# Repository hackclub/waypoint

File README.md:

# Waypoint

Website still a Work in progress! Come back in a week or so!

## Overview

Waypoint is a You Ship, We Ship (YSWS) program where you design your own ROS2 robot.

### You ship:

- A PCB design for your robot
- A chassis design in .STEP format
- A starter ROS2 package for the robot

### We send you:

- A custom Hack Club Waypoint kit!
- A $15 card grant to get your PCB ordered from JLCPCB, and a 3D printed case from [printing legion](https://printlegion.hackclub.com/)!

## Development

The website lives in [`website/`](website).

Run it locally with:

```bash
cd website
npm install
npm run dev
```

## Anything else?

If you're working on Waypoint, start in the guide and website first.

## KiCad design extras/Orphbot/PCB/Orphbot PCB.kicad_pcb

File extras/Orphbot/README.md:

# OrphBot

Orphbot is a 4 wheeled robot with a small lifter on its front. It runs ROS 2 and has a couple autonomous routines.

It serves as an example for the [Waypoint YSWS](https://www.waypoint.hackclub.com), since it implements every component that comes in the kit.

## Renders
*These are optional for submission, but make your design look way cooler!*

## Features:

* A dual color top design
* 128x64 OLED Display
* A 9v Battery
* 6 SK6812 MINI E LEDs
* 4 Drive Motors
* An MPU6050

## CAD:

Everything fits together using 8 M3 Bolts and heatset inserts. Two for the PCB and six for the case.

It has 5 separate 3D printed parts. The main chassis is made up of the lower unibody and top plate, but the design also includes a separate battery cover for easier access as well as a button cover and forks to attach a servo.

## PCB:

Heres what the PCB looks like! It was made in KiCAD.

## Firmware:

This robot uses ROS2! Its package lives in the linked [Firmware](Firmware/) folder, which points to [SharKingStudios/orphbot-package](https://github.com/SharKingStudios/orphbot-package).

* It can connect and display its information to RViz
* It connects to an Xbox controller for control
* The robot can run some simple preprogrammed automous missions
* The OLED displays a small fluid simulation!

## BOM:

The BOM is not included yet.

## Extra stuff

Put something fun or interesting here! Inspiration for the project? Your favorite meme? A joke? Up to you.

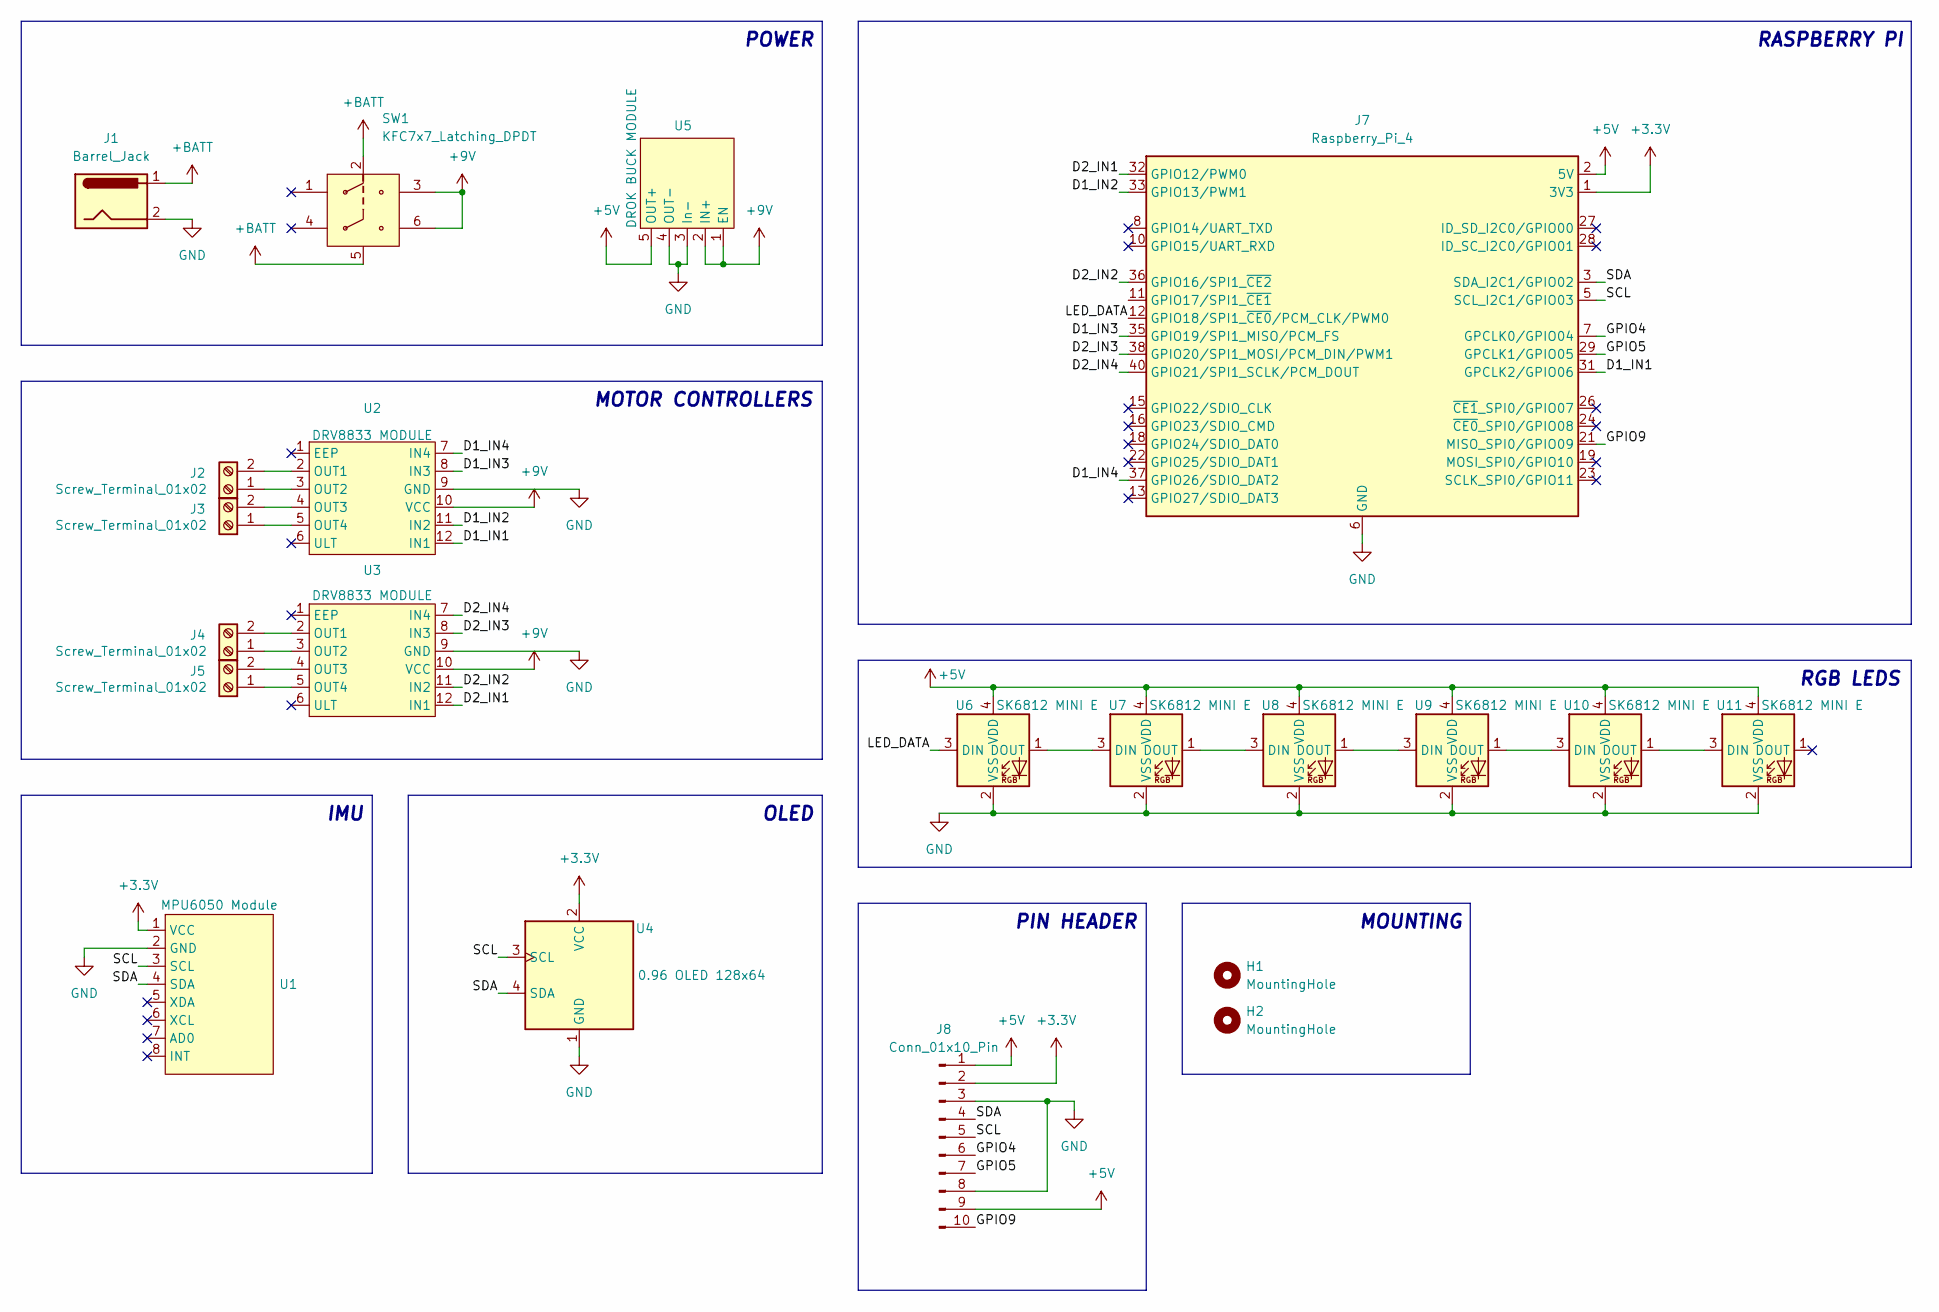
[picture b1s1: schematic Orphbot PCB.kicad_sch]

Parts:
H1, H2: MountingHole; MountingHole_3.2mm_M3_Pad_Via
J1: Barrel_Jack; BarrelJack_Horizontal
J2, J3, J4, J5: Screw_Terminal_01x02; TerminalBlock_KF301-2P_P5.08mm_Blue
J7: Raspberry_Pi_4; MODULE_RASPBERRY_PI_ZERO_2_W
J8: Conn_01x10_Pin; PinHeader_1x10_P2.54mm_Vertical
SW1: KFC7x7_Latching_DPDT; KFC7x7_Latching_DPDT_Blue
U1: MPU6050 Module; LOW_MPU6050_MODULE
U2, U3: DRV8833 MODULE; DRV8833_MODULE
U4: 0.96 OLED 128x64; 128x64OLED
U5: DROK BUCK MODULE; LOW_DROK_BUCK_MODULE
U6, U7, U8, U9, U10, U11: SK6812 MINI E; SK6812MINI_E_CORRECTED

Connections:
+3.3V: J7.1 (3V3), J7.17 (3V3), J8.2, U1.1 (VCC), U4.2 (VCC)
+5V: J7.2 (5V), J7.4 (5V), J8.1, J8.9, U5.5 (OUT+), U6.4 (VDD), U7.4 (VDD), U8.4 (VDD), U9.4 (VDD), U10.4 (VDD), U11.4 (VDD)
+9V: SW1.3, SW1.6, U2.10 (VCC), U3.10 (VCC), U5.1 (EN), U5.2 (IN+)
+BATT: J1.1, SW1.2, SW1.5
/D1_IN1: J7.31 (GPCLK2/GPIO06), U2.12 (IN1)
/D1_IN2: J7.33 (GPIO13/PWM1), U2.11 (IN2)
/D1_IN3: J7.35 (GPIO19/SPI1_MISO/PCM_FS), U2.8 (IN3)
/D1_IN4: J7.37 (GPIO26/SDIO_DAT2), U2.7 (IN4)
/D2_IN1: J7.32 (GPIO12/PWM0), U3.12 (IN1)
/D2_IN2: J7.36 (GPIO16/SPI1_~CE2), U3.11 (IN2)
/D2_IN3: J7.38 (GPIO20/SPI1_MOSI/PCM_DIN/PWM1), U3.8 (IN3)
/D2_IN4: J7.40 (GPIO21/SPI1_SCLK/PCM_DOUT), U3.7 (IN4)
/GPIO4: J7.7 (GPCLK0/GPIO04), J8.6
/GPIO5: J7.29 (GPCLK1/GPIO05), J8.7
/GPIO7: J7.26 (~CE1_SPI0/GPIO07)
/GPIO8: J7.24 (~CE0_SPI0/GPIO08)
/GPIO9: J7.21 (MISO_SPI0/GPIO09), J8.10
/GPIO10: J7.19 (MOSI_SPI0/GPIO10)
/GPIO11: J7.23 (SCLK_SPI0/GPIO11)
/GPIO14: J7.8 (GPIO14/UART_TXD)
/GPIO15: J7.10 (GPIO15/UART_RXD)
/GPIO22: J7.15 (GPIO22/SDIO_CLK)
/GPIO23: J7.16 (GPIO23/SDIO_CMD)
/GPIO24: J7.18 (GPIO24/SDIO_DAT0)
/GPIO25: J7.22 (GPIO25/SDIO_DAT1)
/LED_DATA: J7.12 (GPIO18/SPI1_~CE0/PCM_CLK/PWM0), U6.3 (DIN)
/SCL: J7.5 (SCL_I2C1/GPIO03), J8.5, U1.3 (SCL), U4.3 (SCL)
/SDA: J7.3 (SDA_I2C1/GPIO02), J8.4, U1.4 (SDA), U4.4 (SDA)
GND: J1.2, J7.6 (GND), J7.9 (GND), J7.14 (GND), J7.20 (GND), J7.25 (GND), J7.30 (GND), J7.34 (GND), J7.39 (GND), J8.3, J8.8, U1.2 (GND), U2.9 (GND), U3.9 (GND), U4.1 (GND), U5.3 (In-), U5.4 (OUT-), U6.2 (VSS), U7.2 (VSS), U8.2 (VSS), U9.2 (VSS), U10.2 (VSS), U11.2 (VSS)
unnamed: J2.1, U2.3 (OUT2)
unnamed: J2.2, U2.2 (OUT1)
unnamed: J3.1, U2.5 (OUT4)
unnamed: J3.2, U2.4 (OUT3)
unnamed: J4.1, U3.3 (OUT2)
unnamed: J4.2, U3.2 (OUT1)
unnamed: J5.1, U3.5 (OUT4)
unnamed: J5.2, U3.4 (OUT3)
unnamed: U6.1 (DOUT), U7.3 (DIN)
unnamed: U7.1 (DOUT), U8.3 (DIN)
unnamed: U8.1 (DOUT), U9.3 (DIN)
unnamed: U9.1 (DOUT), U10.3 (DIN)
unnamed: U10.1 (DOUT), U11.3 (DIN)

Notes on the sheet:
MOUNTING
RASPBERRY PI
OLED
PIN HEADER
IMU
MOTOR CONTROLLERS
POWER
RGB LEDS

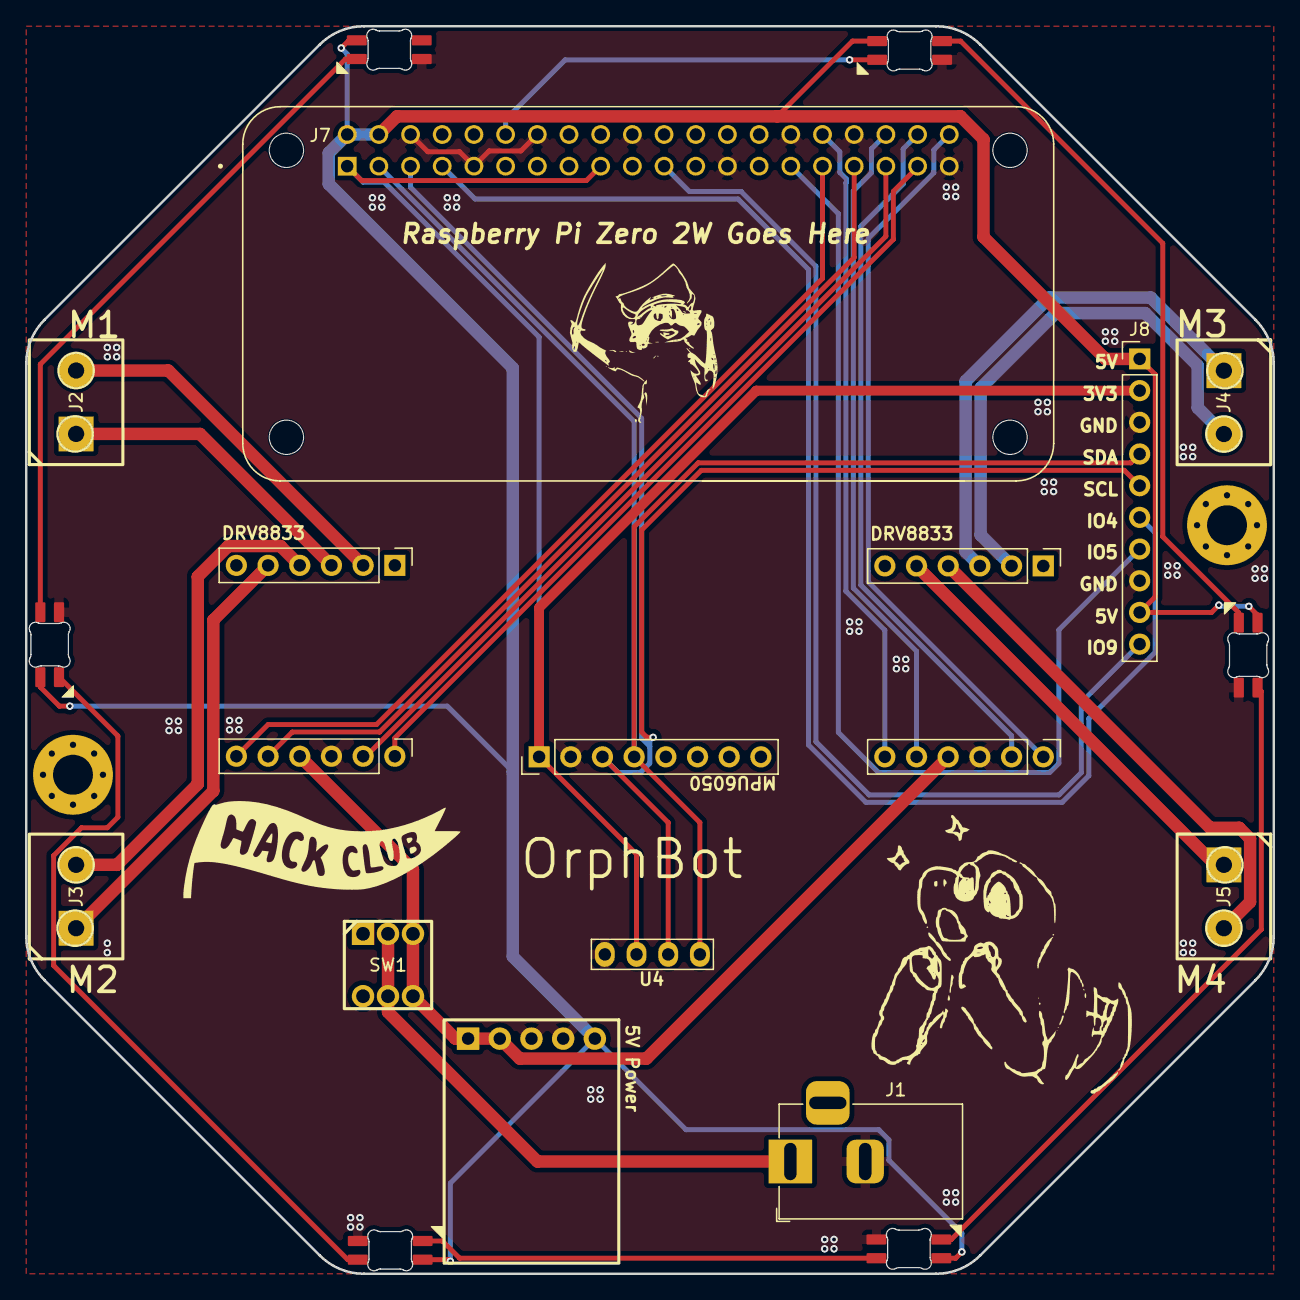
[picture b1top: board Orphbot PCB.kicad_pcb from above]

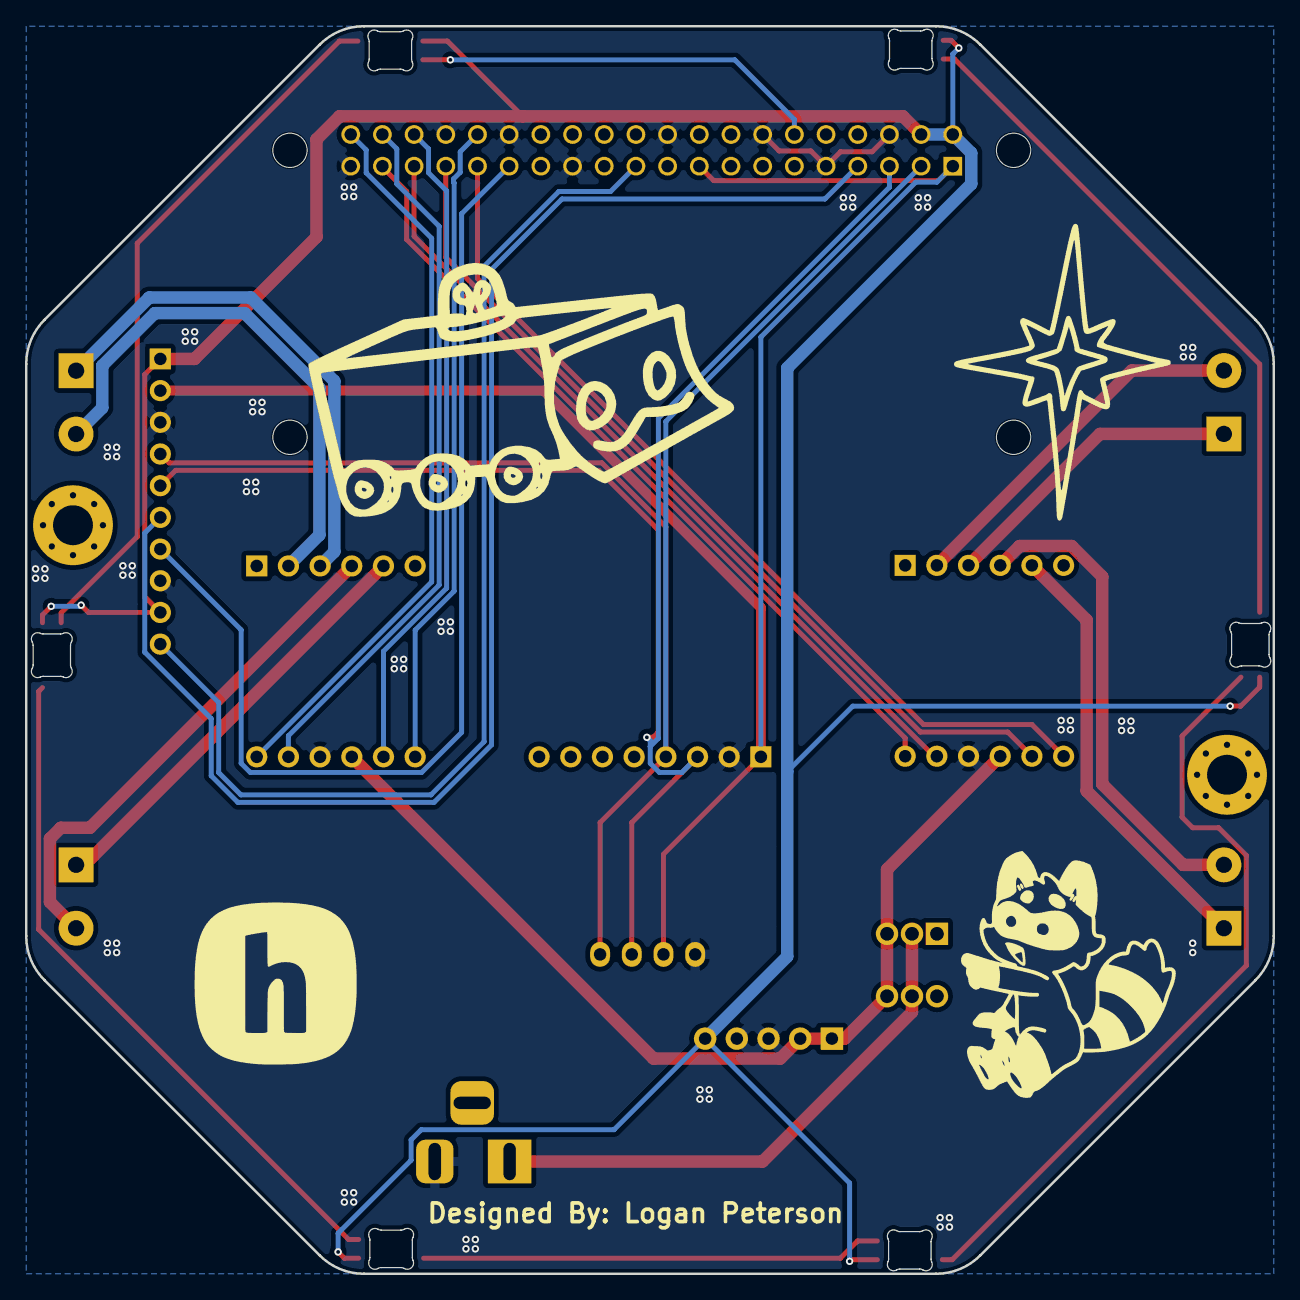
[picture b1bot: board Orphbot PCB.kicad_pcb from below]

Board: 2 copper layers, 100.0 x 100.0 mm, 21 parts (6 on the bottom side), 32 nets.

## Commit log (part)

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2026-04-09 Example Files
2026-04-09 Website *WIP*
2026-04-12 Site Load animation
2026-04-12 Demo init
